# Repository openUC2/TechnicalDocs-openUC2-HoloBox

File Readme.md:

# HoloBox – Modular Interferometry & Digital Holography in a Box

*A fully open-source learning system for optics, interferometry, and holography.*

The **HoloBox** is a modular, open-source toolbox that brings classical and digital optics experiments into classrooms, labs, and maker spaces.
Built on the openUC2 cube system, it enables hands-on experiments ranging from **Michelson/Mach-Zehnder interferometry** to **inline digital holography** and **lensless microscopy**.
The system combines **precise optical hardware**, **open electronics**, and **modern digital workflows** such as **Jupyter notebooks**, **Python image reconstruction**, and **AI-ready embedded cameras**.

The entire project is open-source: hardware, firmware, software, and teaching materials.

## 🚀 What You Can Do With the HoloBox

The HoloBox enables a wide spectrum of optical experiments:

### **Classical Optics & Interference**

* Build and align a **Michelson interferometer**
* Explore the **Mach–Zehnder interferometer**
* Perform **double-slit and grating diffraction**
* Observe **interference fringes**, stability, drift, phase shifts
* Observe temperature induced variations in the **Michelson Interferometer**
* Reconstruct **Inline Holography Microscopy/Digital Holography Microscopy (DHM)** using a Raspberry Pi 
* Visualize thermal expansion by heating one arm of an interferometer

### **Digital Holography**

* Capture **inline holograms** using a point source and the Raspberry Pi Camera
* Reconstruct the hologram numerically using a Python-based UI or Jupyter notebooks
* Perform **digital refocusing**, **Fourier analysis**, and **phase retrieval** (comming soon)
* Understand the connection between physical waves and numerical propagation

### **Lensless Microscopy**

* Image microscopic samples with/without an objective lens
* Detect **microplastics**, **plankton**, or other transparent objects
* Explore Fresnel propagation and digital reconstruction of real samples

### **Interdisciplinary Learning**

* Combine physics with **biology**, **environmental science**, or **computer vision**
* Use programmable electronics (LED modulation, heaters, piezo elements)
* Learn scientific computing through interactive coding tasks

## What’s Included in the Box

The HoloBox comes in two modular versions. Schools, labs, and hackers can start with the **Base Set** and expand later with the **Digital Extension**.

### **1. Base Set – Interferometry & Wave Optics**

Includes everything needed for classical optical experiments:

* Precision openUC2 injection-molded cubes
* 50 mm optical rails & mounts
* Front-surface mirrors
* Beam splitter
* Low-cost laser module
* Screens for fringe observation
* Apertures, slits, gratings
* Worksheets / Wunderbooks
* Printed build instructions

This set enables:

* Michelson interferometer
* Mach–Zehnder interferometer
* Diffraction experiments
* Basic holography (scratch holograms)

#### Inline Holography 

**Reconstruction using the ImSwitch Inline Holography Plugin**

#### Michelson Interferometer

#### Mach Zehnder Interferometer

### **2. Digital Extension – Holography & Computation**

Adds the digital and computational layer:

* **Raspberry Pi Camera** (smart camera that runs our dedicated Operating Sytsem)
* Download the image from here and flash to the SD card https://github.com/openUC2/TechnicalDocs-openUC2-HoloBox/releases/
* Electronics module for:

  * LED control
  * Thermal/piezo phase shifting
  * Triggering and syncing
* Python and Jupyter notebook tutorials
* Digital reconstruction workflows
* Sample experiments (microplastics, plankton, etc.)

This set enables:

* Inline holography
* Hologram reconstruction
* Lensless microscopy
* Computational imaging
* Integration into coding classes

## Modularity & Open-Source Philosophy

The HoloBox is fully modular and open:

* All CAD files are openly published (STL/STEP)
* Parts can be replaced or extended via 3D printing
* Supported by a growing openUC2 community
* Compatible with the UC2 miniBOX, coreBOX, and Quantum MiniLabs
* Designed for repairability and long-term use
* Firmware, software, workflows, and notebooks are open source

The goal:
**Make advanced optics accessible, affordable, and hackable.**

## Getting Started

1. **Get your kits from openUC2**
   Write us a mail: purchase@openuc2.com - STP files will be shared once we're fully done with development

2. **Run your first experiment**
   Choose between Michelson, Mach-Zehnder, diffraction, or holography.

3. **Connect the Raspberry Pi Camera (optional)**
   Start capturing digital holograms or real-time interference patterns. Connect to the Wifi Hotspot (password: `holobox123`) and open the website http://192.168.4.1

4. **Open the Webiste**
   Learn how to:

   * Load holograms
   * Reconstruct using Fresnel propagation
   * Perform digital refocusing
   * Visualize spacetime fringes and frequencies

5. **Modify & extend**
   Print new modules, explore new samples, or write your own analysis scripts.

## Documentation & Resources

Links will be added once this repo structure is finalized.

## Who Is Behind the HoloBox?

The HoloBox is a collaboration between:

* **openUC2 GmbH** – hardware, electronics, software & production
* **University of Münster – Institute for Physics Education** – didactic design & teaching materials
* Supported by regional & national STEM networks

## Roadmap

* Additional digital reconstruction methods
* Phase-shifting holography
* Multi-wavelength illumination
* Plugin for ImSwitch
* Extended classroom activities
* Community-submitted modules

## License

All hardware, firmware, and software are released under open licenses:

* Hardware → **CERN OHL / CC-BY**
* Software → **MIT**
* Teaching materials → **CC-BY**

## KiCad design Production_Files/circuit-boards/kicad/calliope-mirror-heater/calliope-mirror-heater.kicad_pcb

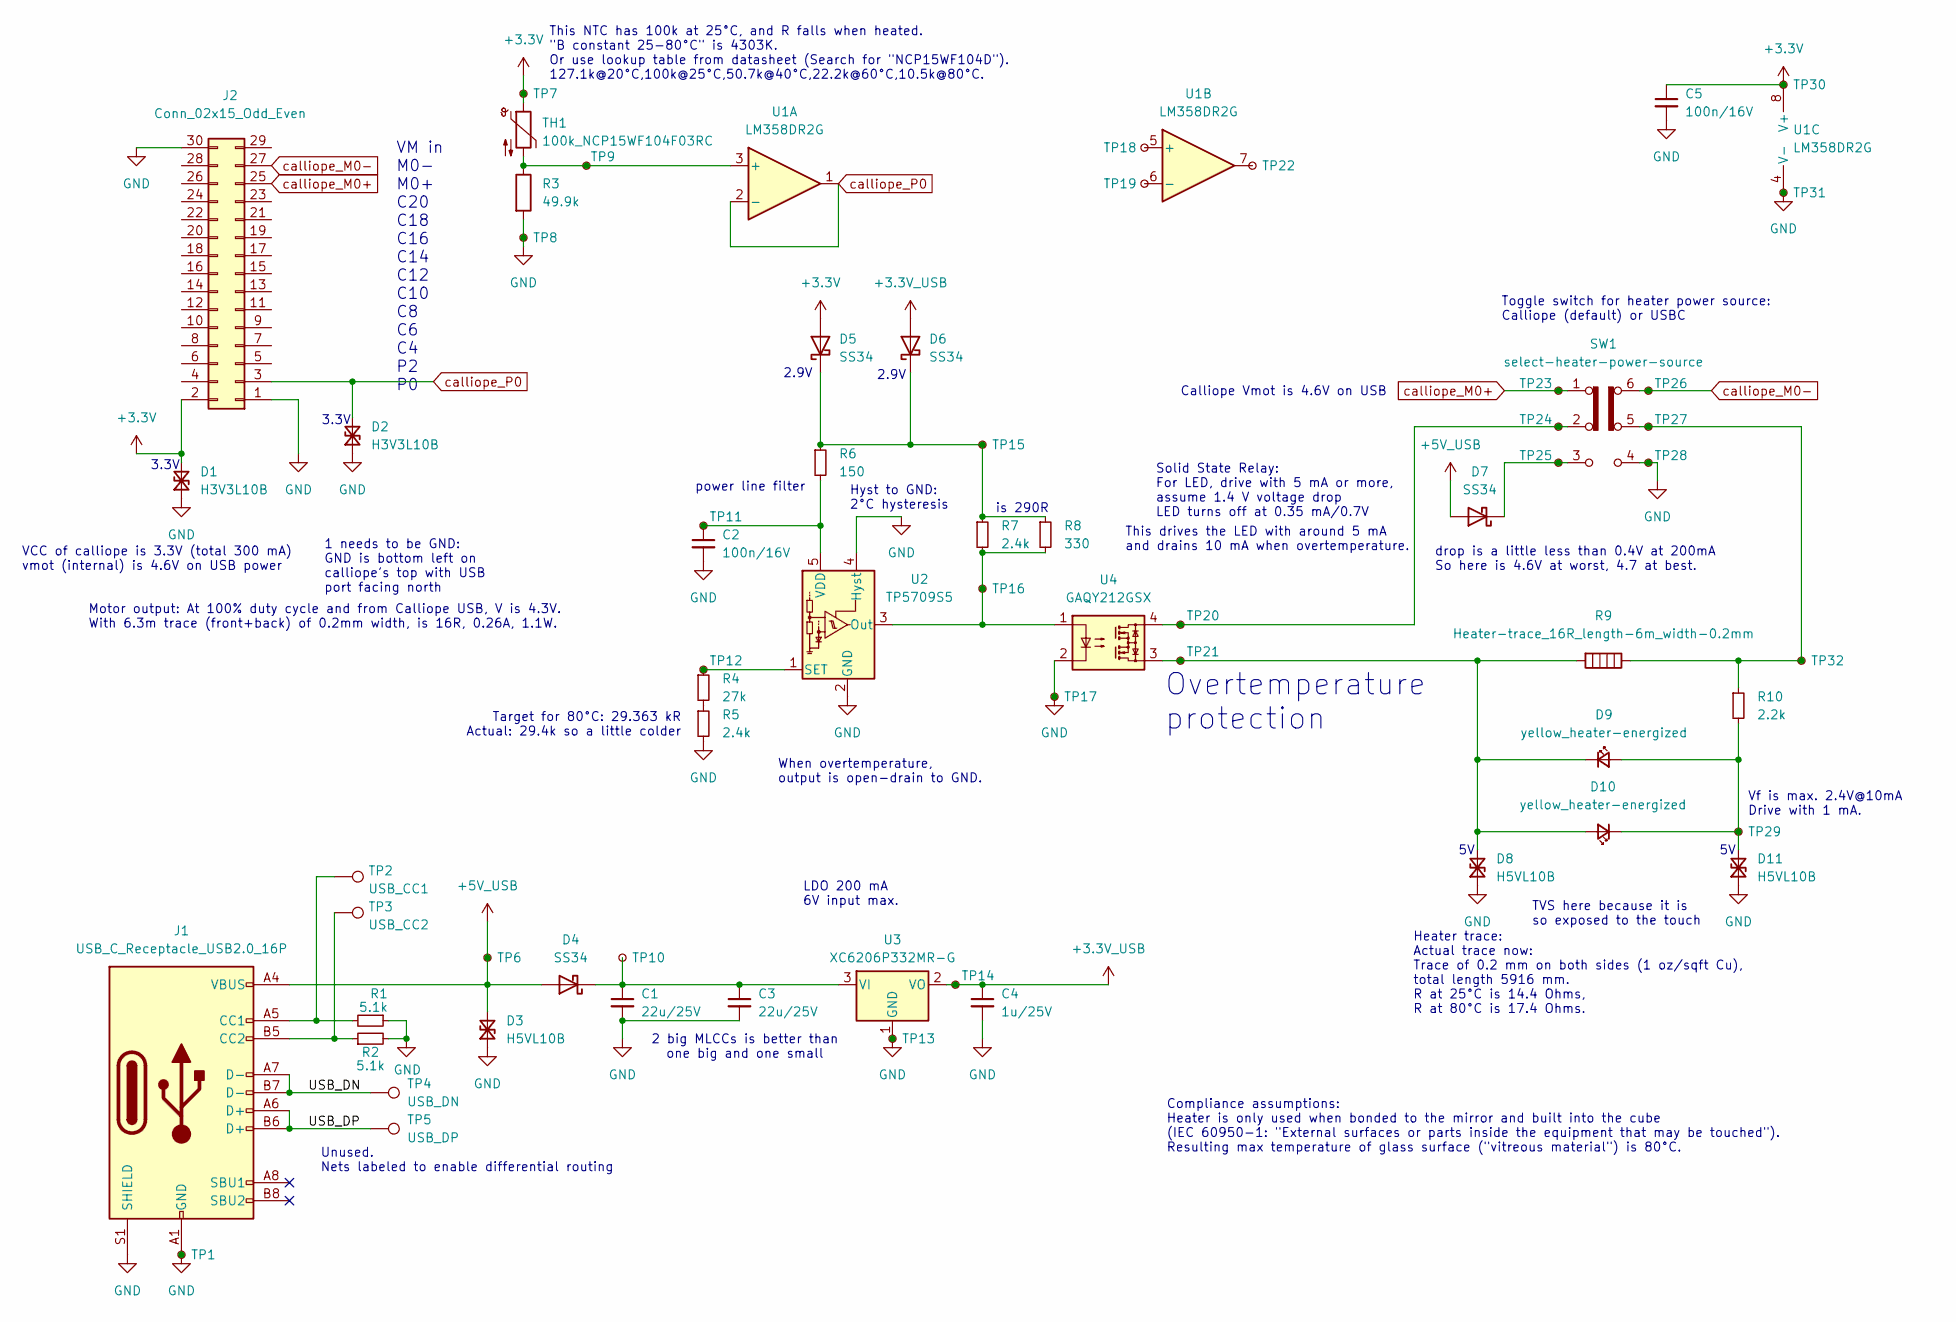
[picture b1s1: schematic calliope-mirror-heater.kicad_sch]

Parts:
C1, C3: 22u/25V; C_0805_2012Metric; LCSC C45783
C2, C5: 100n/16V; C_0402_1005Metric; LCSC C1525
C4: 1u/25V; C_0402_1005Metric; LCSC C52923
D1, D2: H3V3L10B; D_SOD-882D; LCSC C20615781
D3, D8, D11: H5VL10B; D_SOD-882D; LCSC C7420372
D4, D5, D6, D7: SS34; D_SMA; LCSC C8678
D9, D10: yellow_heater-energized; LED_0805_2012Metric; LCSC C2296
J1: USB_C_Receptacle_USB2.0_16P; USB_C_Receptacle_GCT_USB4105-xx-A_16P_TopMnt_Horizontal; LCSC C2765186
J2: Conn_02x15_Odd_Even; PinHeader_2x15_P2.54mm_Horizontal; LCSC C18198029
R1, R2: 5.1k; R_0402_1005Metric; LCSC C25905
R3: 49.9k; R_0402_1005Metric; LCSC C25897
R4: 27k; R_0402_1005Metric; LCSC C25771
R5, R7: 2.4k; R_0402_1005Metric; LCSC C25882
R6: 150; R_0402_1005Metric; LCSC C25082
R8: 330; R_0402_1005Metric; LCSC C25104
R9: Heater-trace_16R_length-6m_width-0.2mm; TestPoint_2Pads_Pitch5.08mm_Drill1.3mm
R10: 2.2k; R_0402_1005Metric; LCSC C25879
SW1: select-heater-power-source; SW_DPDT_shou-han_MST-22D18G2-BD-125; LCSC C20613165
TH1: 100k_NCP15WF104F03RC; R_0402_1005Metric; LCSC C77130
TP1, TP6, TP7, TP8, TP9, TP10, TP11, TP12, TP13, TP14, TP15, TP16, TP17, TP18, TP19, TP20, TP21, TP22, TP23, TP24, TP25, TP26, TP27, TP28, TP29, TP30, TP31, TP32: TestPoint_Small; TestPoint_Pad_D1.0mm
TP2: USB_CC1; TestPoint_Pad_D1.0mm
TP3: USB_CC2; TestPoint_Pad_D1.0mm
TP4: USB_DN; TestPoint_Pad_D1.0mm
TP5: USB_DP; TestPoint_Pad_D1.0mm
U1: LM358DR2G; SOIC-8_3.9x4.9mm_P1.27mm; LCSC C7950
U2: TP5709S5; SOT-23-5; LCSC C2999117
U3: XC6206P332MR-G; SOT-23-3; LCSC XC6206P332MR-G
U4: GAQY212GSX; SO-4_4.4x4.3mm_P2.54mm; LCSC C19271988

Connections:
+3.3V: C5.1, D1.2 (A2), D5.2 (A), J2.2, TH1.1, TP7.1, TP30.1, U1.8 (V+)
+3.3V_USB: C4.1, D6.2 (A), TP14.1, U3.2 (VO)
+5V_USB: D3.2 (A2), D4.2 (A), D7.2 (A), J1.A4 (VBUS), J1.A9 (VBUS), J1.B4 (VBUS), J1.B9 (VBUS), TP6.1
/USB_DN: J1.A7 (D-), J1.B7 (D-), TP4.1
/USB_DP: J1.A6 (D+), J1.B6 (D+), TP5.1
GND: C1.2, C2.2, C3.2, C4.2, C5.2, D1.1 (A1), D2.1 (A1), D3.1 (A1), D8.1 (A1), D11.1 (A1), J1.A1 (GND), J1.A12 (GND), J1.B1 (GND), J1.B12 (GND), J1.S1 (SHIELD), J2.1, J2.30, R1.1, R2.2, R3.2, R5.2, SW1.4 (A), TP1.1, TP8.1, TP13.1, TP17.1, TP28.1, TP31.1, U1.4 (V-), U2.2 (GND), U2.4 (Hyst), U3.1 (GND), U4.2
unnamed: C1.1, C3.1, D4.1 (K), TP10.1, U3.3 (VI)
unnamed: D5.1 (K), D6.1 (K), R6.1, R7.1, R8.1, TP15.1
unnamed: D7.1 (K), SW1.3 (C), TP25.1
unnamed: D8.2 (A2), D9.1 (K), D10.2 (A), R9.2, TP21.1, U4.3
unnamed: D9.2 (A), D10.1 (K), D11.2 (A2), R10.2, TP29.1
unnamed: J1.A5 (CC1), R1.2, TP2.1
unnamed: J1.B5 (CC2), R2.1, TP3.1
unnamed: R4.2, R5.1
unnamed: R9.1, R10.1, SW1.5 (B), TP27.1, TP32.1
unnamed: SW1.2 (B), TP20.1, TP24.1, U4.4
unnamed: TP22.1, U1.7
unnamed: R3.1, TH1.2, TP9.1, U1.3 (+)
unnamed: TP18.1, U1.5 (+)
unnamed: TP19.1, U1.6 (-)
unnamed: R7.2, R8.2, TP16.1, U2.3 (Out), U4.1
unnamed: R4.1, TP12.1, U2.1 (SET)
unnamed: C2.1, R6.2, TP11.1, U2.5 (VDD)
calliope_M0+: J2.25, SW1.1 (A), TP23.1
calliope_M0-: J2.27, SW1.6 (C), TP26.1
calliope_P0: D2.2 (A2), J2.3, U1.1, U1.2 (-)

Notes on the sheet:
VM in M0- M0+ C20 C18 C16 C14 C12 C10 C8 C6 C4 P2 P0
Unused. Nets labeled to enable differential routing
Overtemperature protection
Solid State Relay: For LED, drive with 5 mA or more, assume 1.4 V voltage drop LED turns off at 0.35 mA/0.7V
This drives the LED with around 5 mA and drains 10 mA when overtemperature.
2 big MLCCs is better than one big and one small
is 290R
This NTC has 100k at 25°C, and R falls when heated. "B constant 25-80°C" is 4303K. Or use lookup table from datasheet (Search for "NCP15WF104D"). 127.1k@20°C,100k@25°C,50.7k@40°C,22.2k@60°C,10.5k@80°C.
Calliope Vmot is 4.6V on USB
drop is a little less than 0.4V at 200mA So here is 4.6V at worst, 4.7 at best.
Target for 80°C: 29.363 kR Actual: 29.4k so a little colder
Vf is max. 2.4V@10mA Drive with 1 mA.
Motor output: At 100% duty cycle and from Calliope USB, V is 4.3V. With 6.3m trace (front+back) of 0.2mm width, is 16R, 0.26A, 1.1W.
Compliance assumptions: Heater is only used when bonded to the mirror and built into the cube (IEC 60950-1: "External surfaces or parts inside the equipment that may be touched"). Resulting max temperature of glass surface ("vitreous material") is 80°C.
3.3V
TVS here because it is so exposed to the touch
Toggle switch for heater power source: Calliope (default) or USBC
1 needs to be GND: GND is bottom left on calliope's top with USB port facing north
2.9V
LDO 200 mA 6V input max.
Hyst to GND: 2°C hysteresis
When overtemperature, output is open-drain to GND.
Heater trace: Actual trace now: Trace of 0.2 mm on both sides (1 oz/sqft Cu), total length 5916 mm. R at 25°C is 14.4 Ohms, R at 80°C is 17.4 Ohms.
VCC of calliope is 3.3V (total 300 mA) vmot (internal) is 4.6V on USB power
power line filter

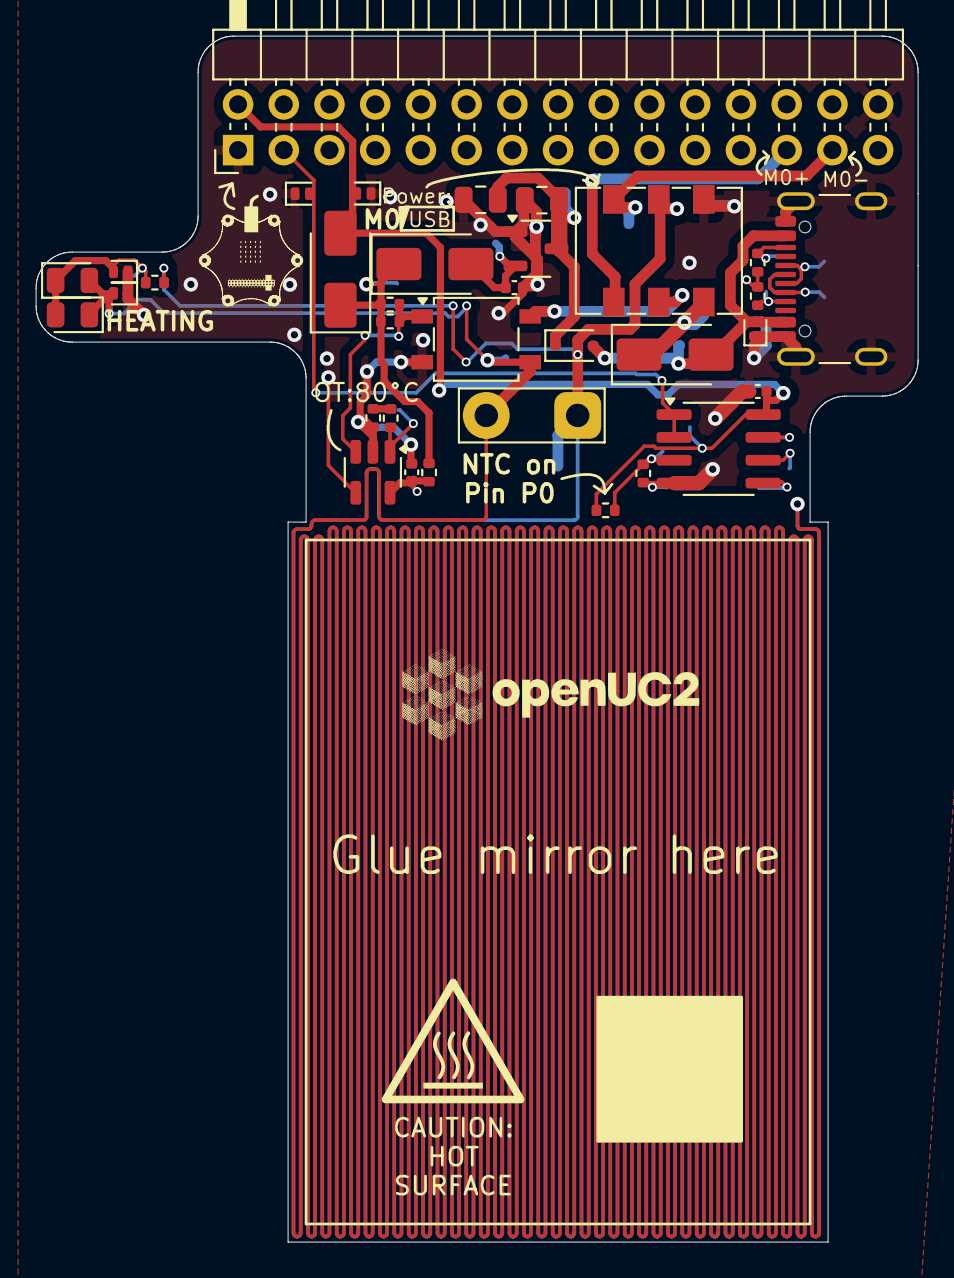
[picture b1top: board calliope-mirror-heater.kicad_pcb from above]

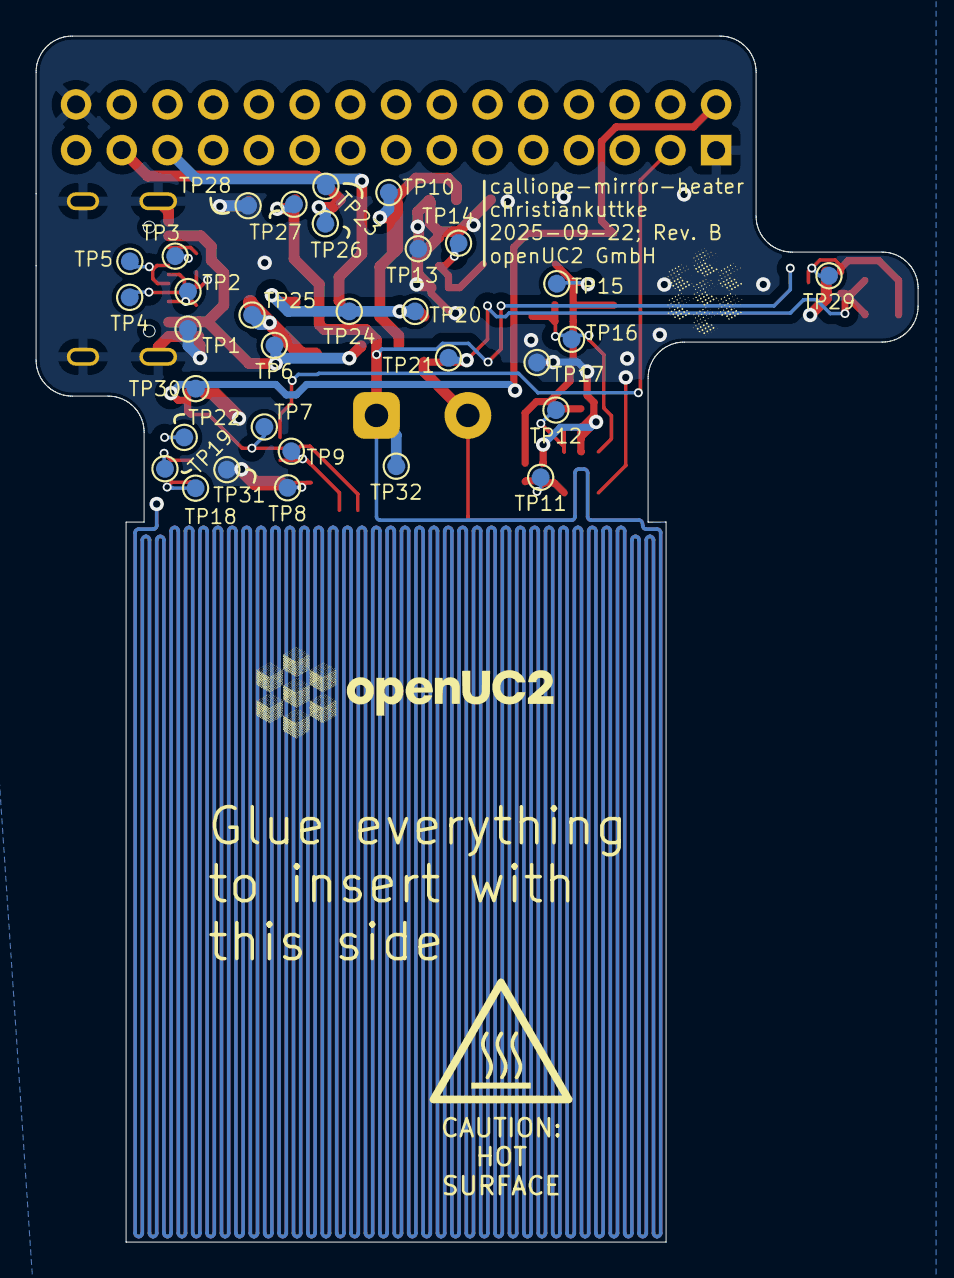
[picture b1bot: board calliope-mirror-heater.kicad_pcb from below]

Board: 2 copper layers, 49.0 x 67.0 mm, 66 parts (32 on the bottom side), 26 nets.

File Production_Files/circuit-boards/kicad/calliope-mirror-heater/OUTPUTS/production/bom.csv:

Designator,Footprint,Quantity,Value,LCSC Part #
"C1, C3",0805,2,22u/25V,C45783
"C2, C5",0402,2,100n/16V,C1525
C4,0402,1,1u/25V,C52923
"D1, D2",D_SOD-882D,2,H3V3L10B,C20615781
"D10, D9",0805,2,yellow_heater-energized,C2296
"D11, D3, D8",D_SOD-882D,3,H5VL10B,C7420372
D4,D_SOD-323,1,1N5819WS,C191023
"D5, D6, D7",D_SMA,3,SS34,C8678
J1,USB_C_Receptacle_GCT_USB4105-xx-A_16P_TopMnt_Horizontal,1,USB_C_Receptacle_USB2.0_16P,C2765186
J2,PinHeader_2x15_P2.54mm_Horizontal,1,Conn_02x15_Odd_Even,C18198029
"R1, R2",0402,2,5.1k,C25905
R10,0402,1,2.2k,C25879
R3,0402,1,49.9k,C25897
R4,0402,1,27k,C25771
"R5, R7",0402,2,2.4k,C25882
R6,0402,1,150,C25082
R8,0402,1,330,C25104
R9,TestPoint_2Pads_Pitch5.08mm_Drill1.3mm,1,Heater-trace_16R_length-6m_width-0.2mm,
SW1,SW_DPDT_shou-han_MST-22D18G2-BD-125,1,select-heater-power-source,C20613165
TH1,0402,1,100k_NCP15WF104F03RC,C77130
"TP1, TP10, TP11, TP12, TP13, TP14, TP15, TP16, TP17, TP18, TP19, TP20, TP21, TP22, TP23, TP24, TP25, TP26, TP27, TP28, TP29, TP30, TP31, TP32, TP6, TP7, TP8, TP9",TestPoint_Pad_D1.0mm,28,TestPoint_Small,
TP2,TestPoint_Pad_D1.0mm,1,USB_CC1,
TP3,TestPoint_Pad_D1.0mm,1,USB_CC2,
TP4,TestPoint_Pad_D1.0mm,1,USB_DN,
TP5,TestPoint_Pad_D1.0mm,1,USB_DP,
U1,SOIC-8_3.9x4.9mm_P1.27mm,1,LM358DR2G,C7950
U2,SOT-23-5,1,TP5709S5,C2999117
U3,SOT-23-3,1,XC6206P332MR-G,XC6206P332MR-G
U4,SO-4_4.4x4.3mm_P2.54mm,1,GAQY212GSX,C19271988

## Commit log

2025-06-01 adding first version of camera server
2025-06-12 adding jupyter notebook and index for camera streaming
2025-06-12 Initial plan for issue
2025-06-12 Implement streamlined camera API and hologram processing interface
2025-06-12 Add demo script for easy system startup and testing
2025-06-12 Fix CORS and PyScript issues, add SSL support for GitHub Pages integration
2025-06-13 cleaning up files
2025-06-13 Split HTML/JS/PyScript into separate files and fix function parameter and cross-origin issues
2025-06-13 Add comprehensive validation tests for refactored code
2025-06-13 Add comprehensive debugging capabilities and fix array broadcasting issue
2025-06-13 updating code
2025-06-13 Fix PyScript proxy destruction error in hologram processing
2025-06-16 Implement automatic SSL certificate generation on first launch
2025-06-17 Implement autostart camera server with Access Point and WiFi management
2025-06-18 Add comprehensive educational Jupyter notebook for hologram processing
2025-06-22 Create offline Jupyter notebook with hologram processing capabilities
2025-06-22 Complete offline Jupyter notebook implementation with comprehensive testing
2025-06-22 Add integration examples and quick start guide for offline notebook
2025-06-22 minor changes
2025-06-22 Replace PyScript with JupyterLite implementation and CLI build system
2025-06-22 Add gitignore for JupyterLite build artifacts and clean up
2025-06-22 Implement xeus-lite-demo template with GitHub Actions deployment
2025-07-07 Initial plan
2025-07-07 Implement SD card image build system with GitHub Actions
2025-07-07 Add demo script and finalize SD card image build system
2025-07-07 Fix e2fsck interactive mode issue in GitHub Actions
2025-07-16 add files
2025-07-16 fix typo
2025-07-17 fixing typo
2025-07-28 moving away from venv and adding picamera via apt-get
2025-07-30 ensure right versions
2025-07-30 update dependencies
2025-07-31 changing order
2025-08-13 Implement MAC-based SSID generation with openUC2-NAME1-NAME2 format
2025-08-13 Add comprehensive documentation for MAC-based SSID generation
2025-08-14 Fix user setup and access point startup issues
2025-08-14 Implement comprehensive first-boot auto-login solution for HoloBox
2025-08-23 Enhance HoloBox SD Card Image build with NetworkManager AP
    Updated the build workflow for HoloBox SD Card Image to include NetworkManager AP configuration and adjusted package installations accordingly.
2025-08-23 Refactor HoloBox SD Card Image build workflow
2025-08-24 Add libcap-dev to package installation
2025-08-24 Implement offline functionality and URL redirection for HoloBox web interface
2025-08-25 Add new STL files and archive old CAD files
    Added multiple new STL files for KIT - HOLO - HOL-25-01_PRT components in the PRINTING directory. Archived previous CAD files by moving them to the PRINTING_OLD directory to maintain version history 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
2025-08-25 update build script
2025-08-25 Update Pi Zero camera setup and troubleshooting docs
    Simplified Pi Zero camera package installation in build workflow by always installing libcamera packages. Expanded README with detailed camera detection, troubleshooting steps, and legacy camera test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
2025-08-25 update lib
2025-08-27 Implement comprehensive HoloBox offline improvements
    - Replace CDN dependencies with local bootstrap-minimal.css
    - Add boundary box overlay with adjustable positioning
    - Implement default IP suggestion (192.168.4.1:8000)
    - Add +/- buttons to sliders for precise mobile control
    - Implement image orientation controls (Flip X/Y, Rotate 90°)
    - Fix aspect ratio with object-fit: contain
2025-08-27 Implement core offline Pi imaging improvements: IP defaults, slider controls, image orientation, boundary box
2025-08-30 Implement advanced hologram processing features: HTTP protocol, auto URL detection, full rotation controls, square ROI, and color channel selection
2025-08-31 Refactor and reorganize Software directory
    Moved documentation files to Software/DOCS, relocated test scripts to Software/test, and added Pyodide and Pyscript assets for offline functionality. Removed obsolete files and cleaned up old images,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
2025-08-31 Revamp PyScript to use local files and simplified pattern
2025-08-31 Fix event handling and complete simplified PyScript implementation
2025-08-31 Improve ROI handling and event proxying for hologram processing
    Enhanced boundary box coordinate calculation in camera_controls.js and integrated it with hologram_processing.py for more accurate ROI selection. Updated image processing to crop and transform the se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
2025-08-31 Add dark theme UI and improve hologram processing
    Introduces a comprehensive dark theme to the web interface, including new assets and updated styles in index.html. Refactors hologram_processing.py to handle full-resolution images, robust ROI extrac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
2025-09-12 Roughly finished schematic for calliope mirror heater experiment
2025-09-17 Implement enhanced camera API with HTTP-only, new controls, and cross-browser compatibility
2025-09-19 fix loading issues
2025-09-19 fixing sudo problems with port
2025-09-19 Implement off-axis hologram reconstruction web interface
2025-09-19 addings docs for sample prep
2025-09-19 Electrically done
2025-09-20 fixing streaming issues
2025-09-21 Finished calliope board! Ready to export production files.
2025-09-22 Change default SSH password from 'holobox123' to 'youseetoo'
    Updated default SSH password in README.
2025-09-22 Finished Rev B: correct slide-switch fp
2025-09-22 Generated production files and verified JLC upload OK!
2025-10-02 Add JavaScript fallback for PyScript on iOS/iPad devices
2025-10-02 Add fallback support for off-axis page and comprehensive documentation
2025-10-02 Add validation and test infrastructure for fallback system
2025-10-02 Add Quick Start guide for fallback system
2025-10-02 Add comprehensive README overview for fallback system
2025-10-02 Add high-res snap feature and static image processing
    Introduces a 'Snap High-Res' button to the camera controls, enabling users to capture and process a high-resolution (1920x1080) static image. Updates frontend and backend to support seamless switchin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
2025-10-03 Ensure it works on ipad
2025-10-09 Improve SD image workflow and fix image cropping bug
    Enhanced the GitHub Actions workflow to support manual release tagging, prerelease flag, and automated release asset uploads. Refactored the SSID generation and AP configuration scripts for first-boo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
2025-10-16 Add calliope makecode sketch for mirror-heater
2025-11-12 fixing wifi hotspot, cleaning up
2025-11-20 adding documentation
2025-11-20 reorganize readmes
2026-01-07 adding docs
